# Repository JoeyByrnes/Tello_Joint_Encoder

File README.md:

# Tello_Joint_Encoder
PCB Design Files and Firmware for Tello Joint Encoders

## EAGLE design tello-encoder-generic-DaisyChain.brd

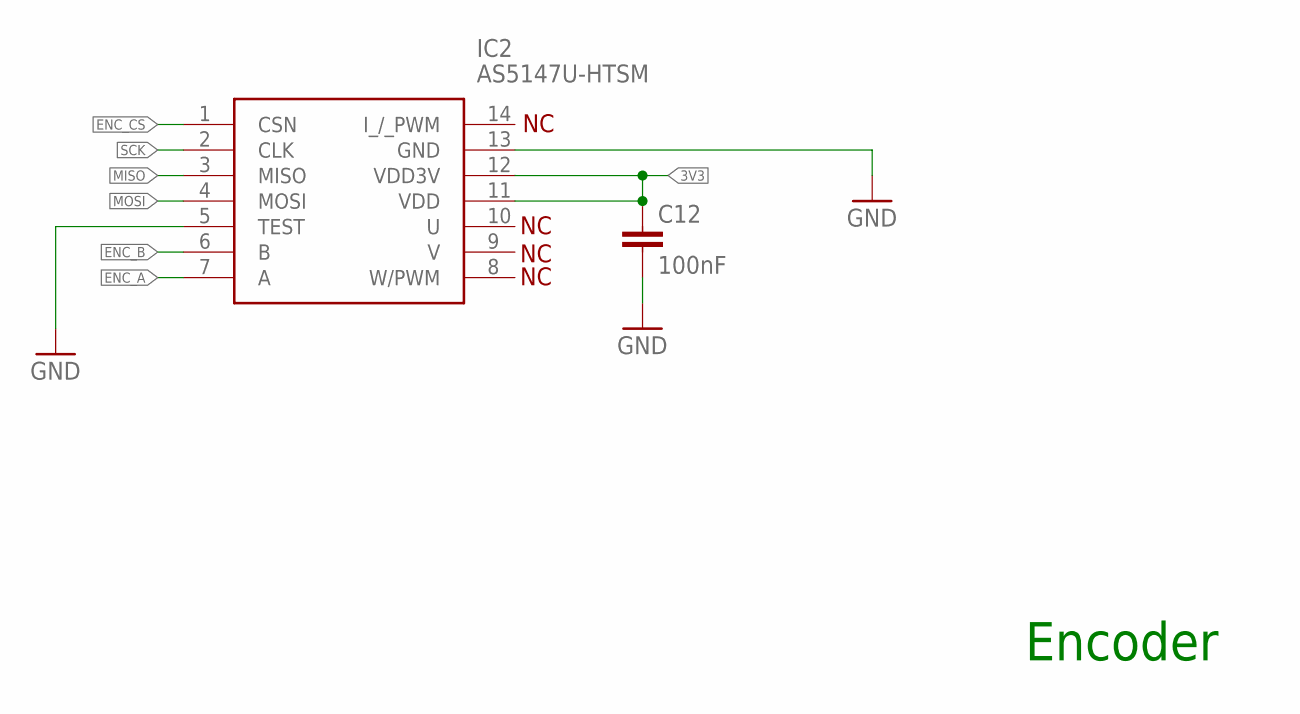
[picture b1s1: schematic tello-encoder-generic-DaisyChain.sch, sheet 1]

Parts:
C12: 100nF; C0402
IC2: AS5147U-HTSM; SOP65P640X120-14N

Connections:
3V3: C12.1, IC2.11 (VDD), IC2.12 (VDD3V); also elsewhere on the board
ENC_A: IC2.7 (A); also elsewhere on the board
ENC_B: IC2.6 (B); also elsewhere on the board
ENC_CS: IC2.1 (CSN); also elsewhere on the board
GND: C12.2, IC2.5 (TEST), IC2.13 (GND); also elsewhere on the board
MISO: IC2.3 (MISO); also elsewhere on the board
MOSI: IC2.4 (MOSI); also elsewhere on the board
SCK: IC2.2 (CLK); also elsewhere on the board

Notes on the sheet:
Encoder

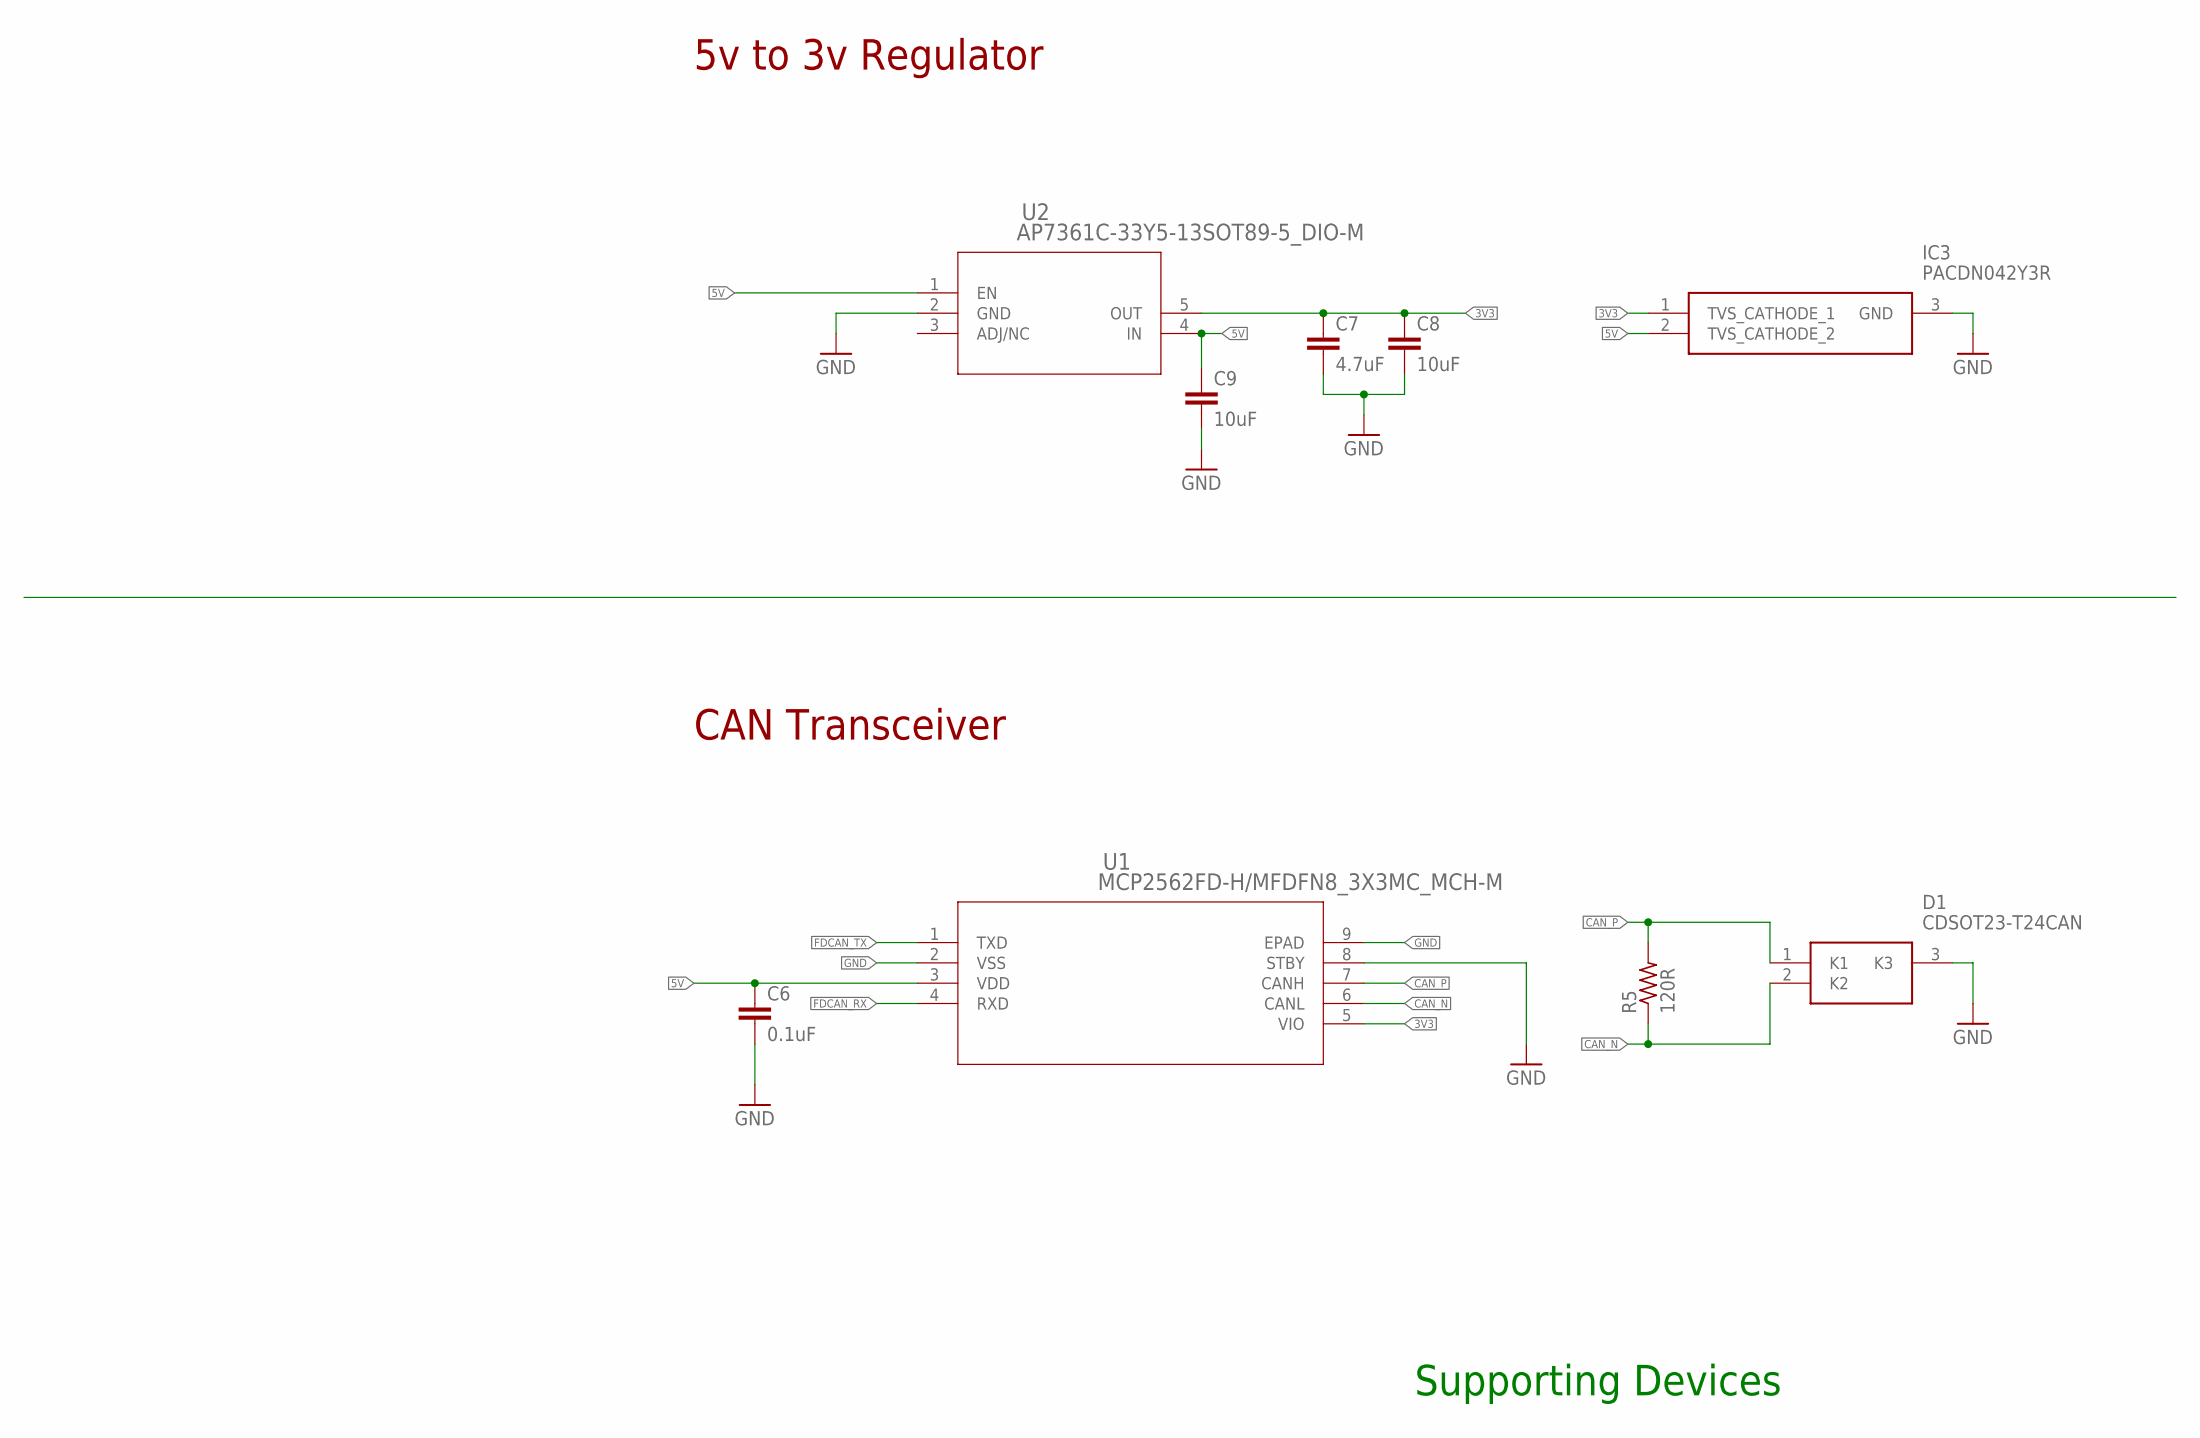
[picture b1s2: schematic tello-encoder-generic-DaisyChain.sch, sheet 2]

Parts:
C6: 0.1uF; C0603
C7: 4.7uF; C0603
C8, C9: 10uF; C0603
D1: CDSOT23-T24CAN; SOT95P230X117-3N
IC3: PACDN042Y3R; SOT96P237X111-3N
R5: 120R; R0402
U1: MCP2562FD-H/MFDFN8_3X3MC_MCH-M; DFN8_3X3MC_MCH-M
U2: AP7361C-33Y5-13SOT89-5_DIO-M; SOT89-5_DIO-M

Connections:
3V3: C7.1, C8.1, IC3.1 (TVS_CATHODE_1), U1.5 (VIO), U2.5 (OUT); also elsewhere on the board
5V: C6.1, C9.1, IC3.2 (TVS_CATHODE_2), U1.3 (VDD), U2.1 (EN), U2.4 (IN); also elsewhere on the board
CAN_N: D1.2 (K2), R5.1, U1.6 (CANL); also elsewhere on the board
CAN_P: D1.1 (K1), R5.2, U1.7 (CANH); also elsewhere on the board
FDCAN_RX: U1.4 (RXD); also elsewhere on the board
FDCAN_TX: U1.1 (TXD); also elsewhere on the board
GND: C6.2, C7.2, C8.2, C9.2, D1.3 (K3), IC3.3 (GND), U1.2 (VSS), U1.8 (STBY), U1.9 (EPAD), U2.2 (GND); also elsewhere on the board

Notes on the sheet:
5v to 3v Regulator
CAN Transceiver
Supporting Devices

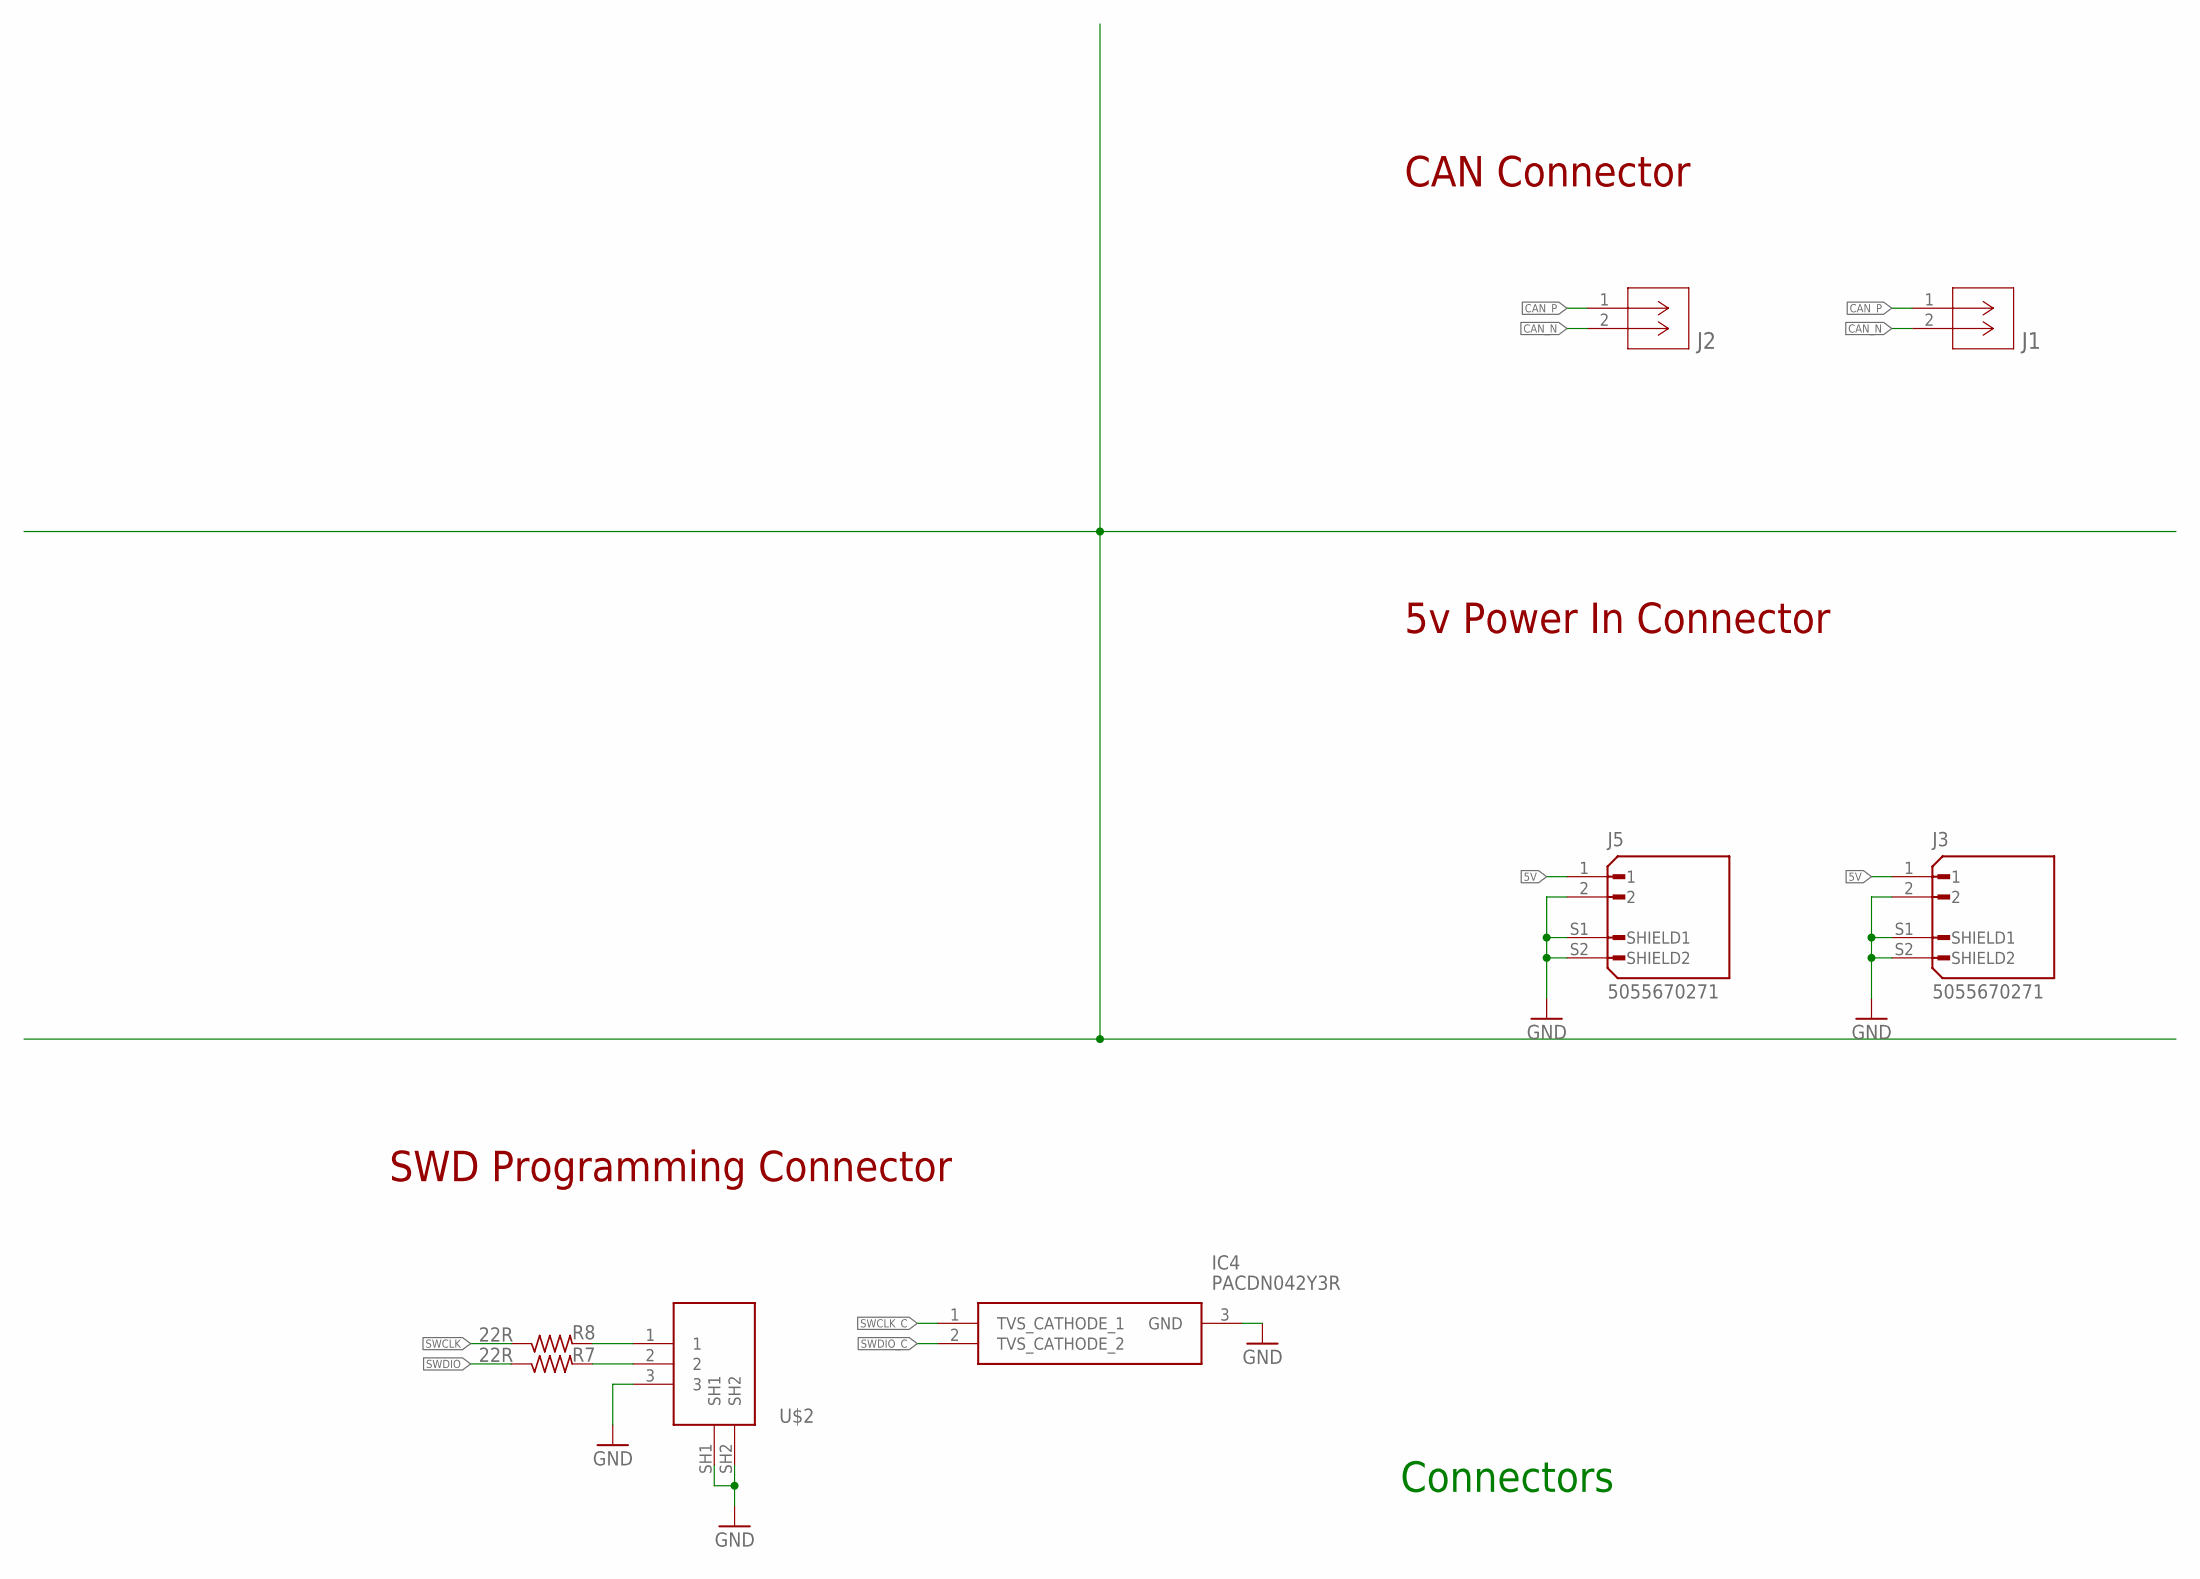
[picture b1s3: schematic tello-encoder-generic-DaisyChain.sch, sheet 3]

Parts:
IC4: PACDN042Y3R; SOT96P237X111-3N
J1, J2: SM02BGHSTBLFSN; CONN_SM02BGHSTB_JST
J3, J5: 5055670271; MOLEX_5055670271
R7, R8: 22R; R0402
U$2: 125SH-G-03-TR-SMT

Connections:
5V: J3.1, J5.1; also elsewhere on the board
CAN_N: J1.2, J2.2; also elsewhere on the board
CAN_P: J1.1, J2.1; also elsewhere on the board
GND: IC4.3 (GND), J3.2, J3.S1 (SHIELD1), J3.S2 (SHIELD2), J5.2, J5.S1 (SHIELD1), J5.S2 (SHIELD2), U$2.3, U$2.SH1, U$2.SH2; also elsewhere on the board
SWCLK: R8.1; also elsewhere on the board
SWCLK_C: IC4.1 (TVS_CATHODE_1), R8.2, U$2.1
SWDIO: R7.1; also elsewhere on the board
SWDIO_C: IC4.2 (TVS_CATHODE_2), R7.2, U$2.2

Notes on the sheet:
U$2
CAN Connector
5v Power In Connector
SWD Programming Connector
Connectors

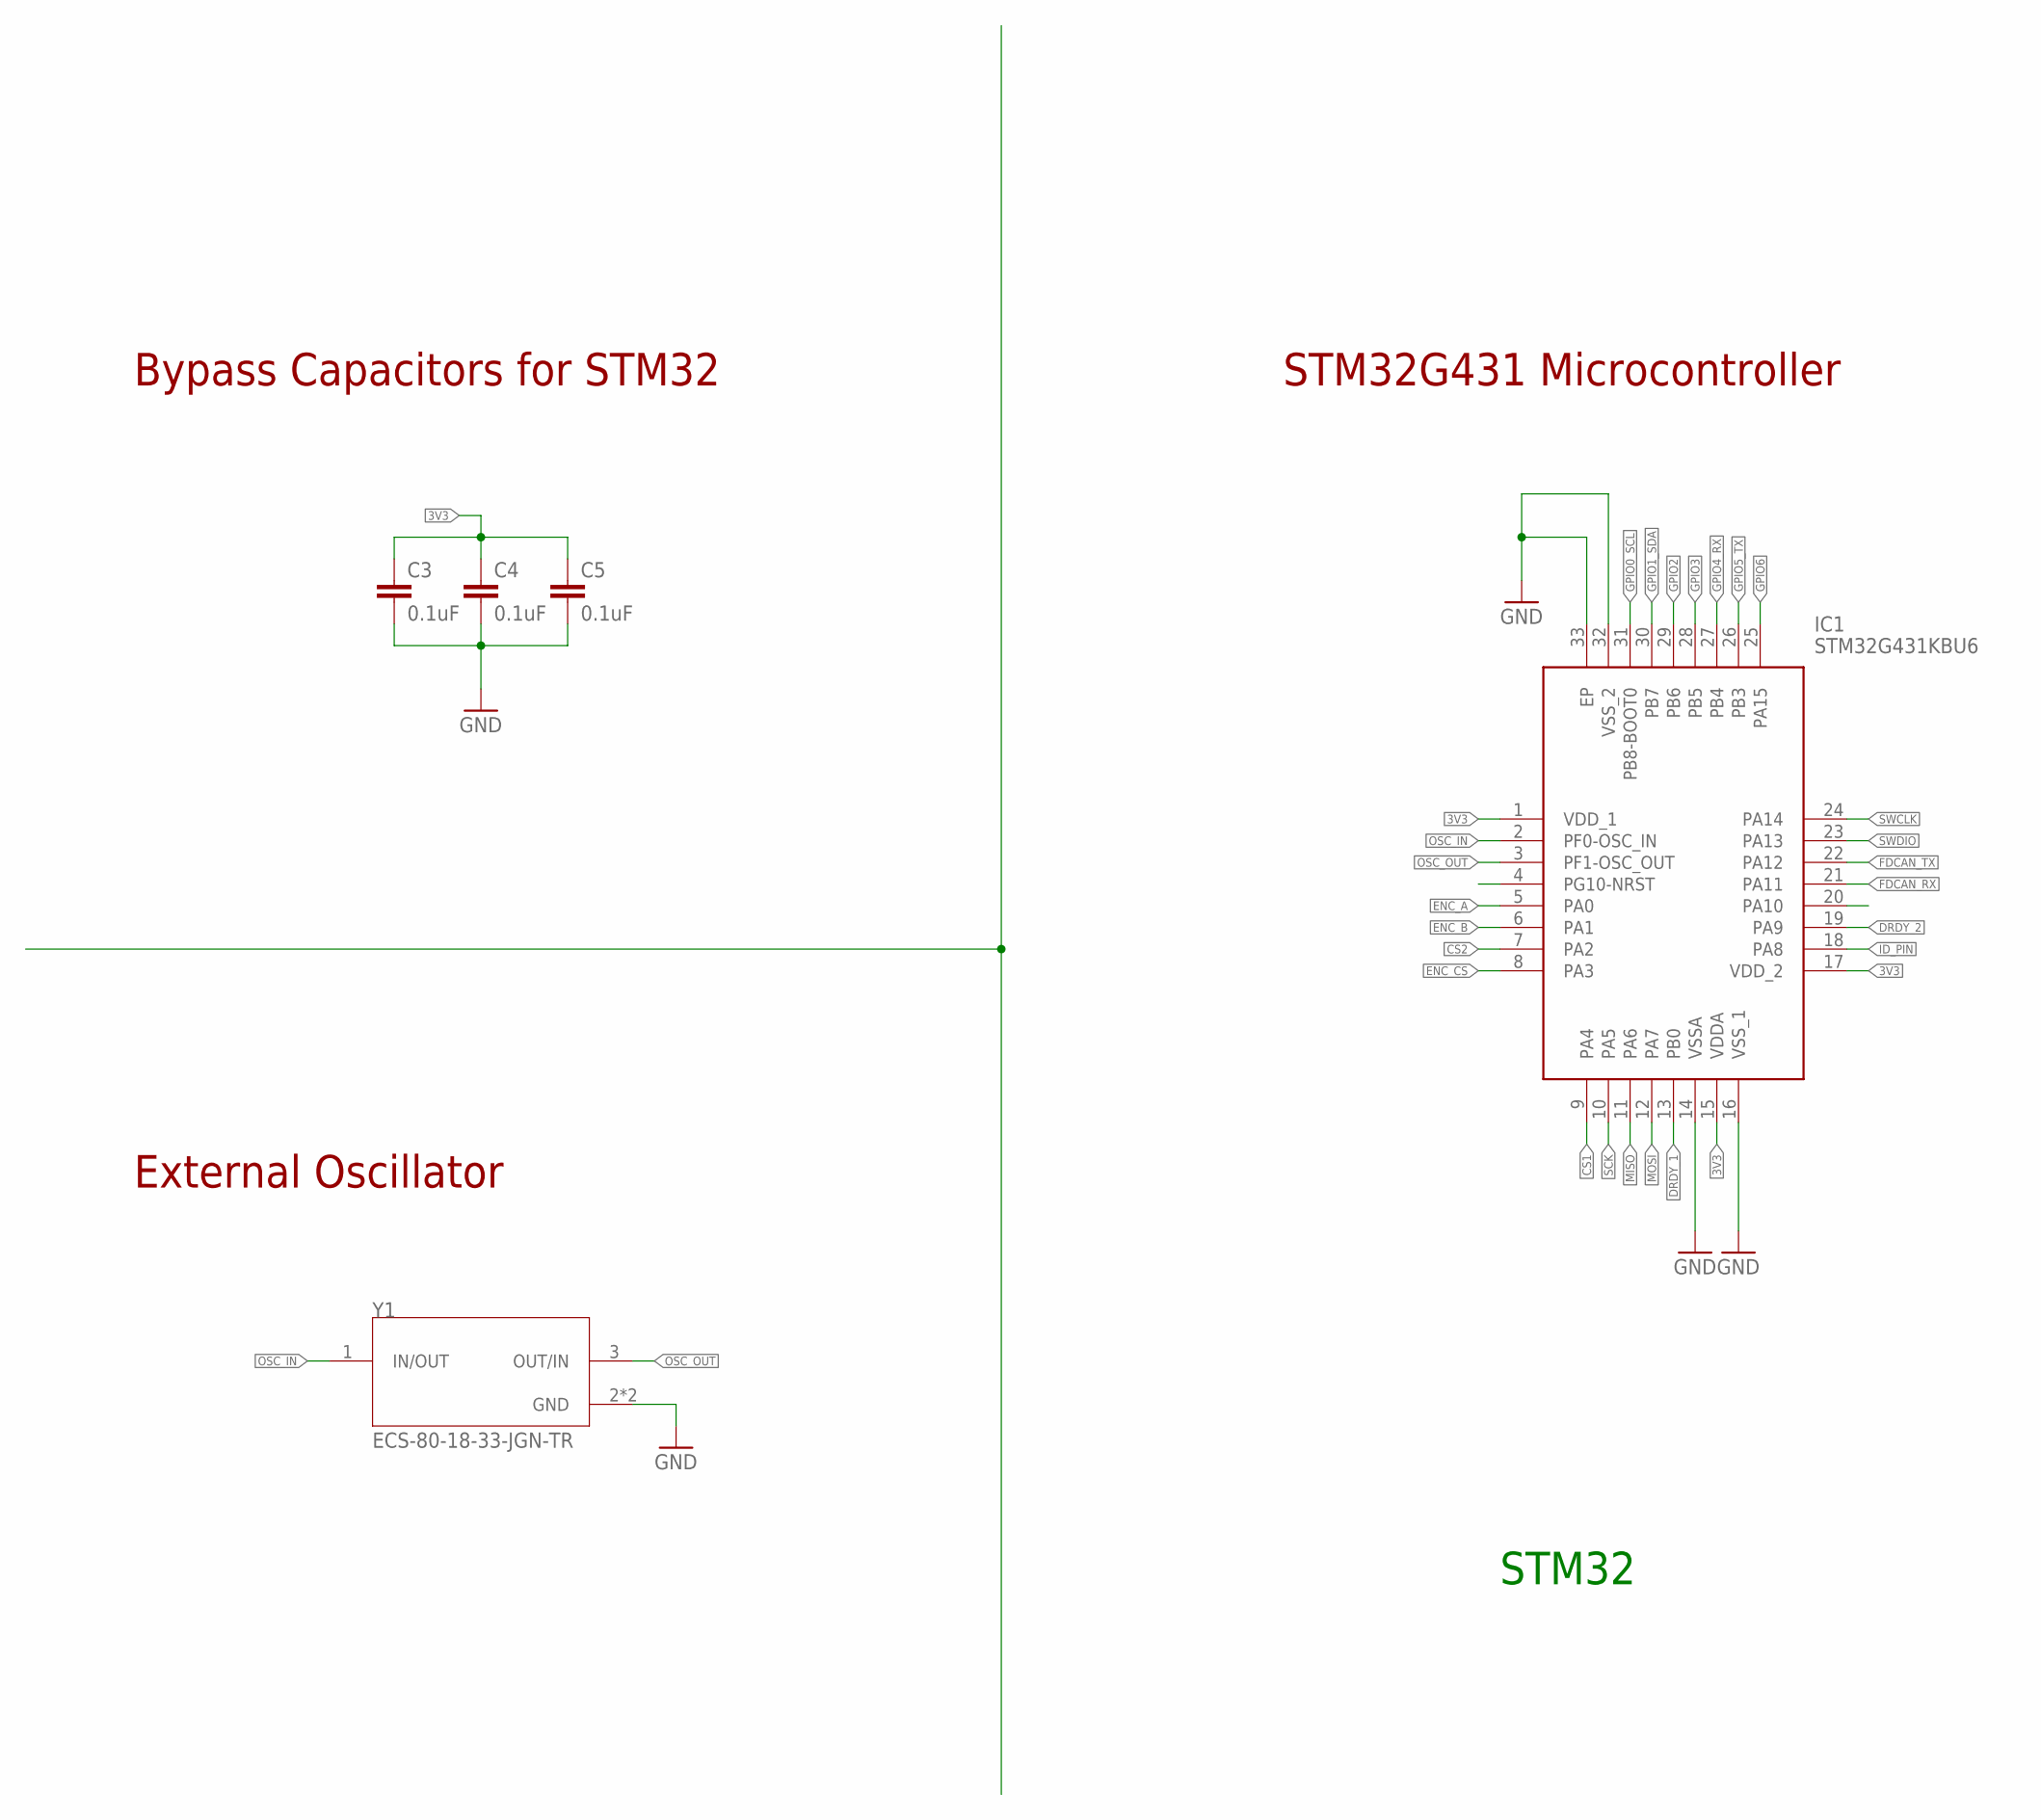
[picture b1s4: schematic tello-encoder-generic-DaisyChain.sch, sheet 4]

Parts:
C3, C4, C5: 0.1uF; C0402
IC1: STM32G431KBU6; QFN50P500X500X60-33N
Y1: ECS-80-18-33-JGN-TR; XTAL_ECS-240-8-33-AGN-TR

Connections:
3V3: C3.1, C4.1, C5.1, IC1.1 (VDD_1), IC1.15 (VDDA), IC1.17 (VDD_2); also elsewhere on the board
CS1: IC1.9 (PA4)
CS2: IC1.7 (PA2)
DRDY_1: IC1.13 (PB0)
DRDY_2: IC1.19 (PA9)
ENC_A: IC1.5 (PA0); also elsewhere on the board
ENC_B: IC1.6 (PA1); also elsewhere on the board
ENC_CS: IC1.8 (PA3); also elsewhere on the board
FDCAN_RX: IC1.21 (PA11); also elsewhere on the board
FDCAN_TX: IC1.22 (PA12); also elsewhere on the board
GND: C3.2, C4.2, C5.2, IC1.14 (VSSA), IC1.16 (VSS_1), IC1.32 (VSS_2), IC1.33 (EP), Y1.2 (GND), Y1.4 (GND); also elsewhere on the board
GPIO0_SCL: IC1.31 (PB8-BOOT0)
GPIO1_SDA: IC1.30 (PB7)
GPIO2: IC1.29 (PB6)
GPIO3: IC1.28 (PB5)
GPIO4_RX: IC1.27 (PB4)
GPIO5_TX: IC1.26 (PB3)
GPIO6: IC1.25 (PA15)
ID_PIN: IC1.18 (PA8)
MISO: IC1.11 (PA6); also elsewhere on the board
MOSI: IC1.12 (PA7); also elsewhere on the board
OSC_IN: IC1.2 (PF0-OSC_IN), Y1.1 (IN/OUT)
OSC_OUT: IC1.3 (PF1-OSC_OUT), Y1.3 (OUT/IN)
SCK: IC1.10 (PA5); also elsewhere on the board
SWCLK: IC1.24 (PA14); also elsewhere on the board
SWDIO: IC1.23 (PA13); also elsewhere on the board

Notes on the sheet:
Bypass Capacitors for STM32
External Oscillator
STM32G431 Microcontroller
STM32

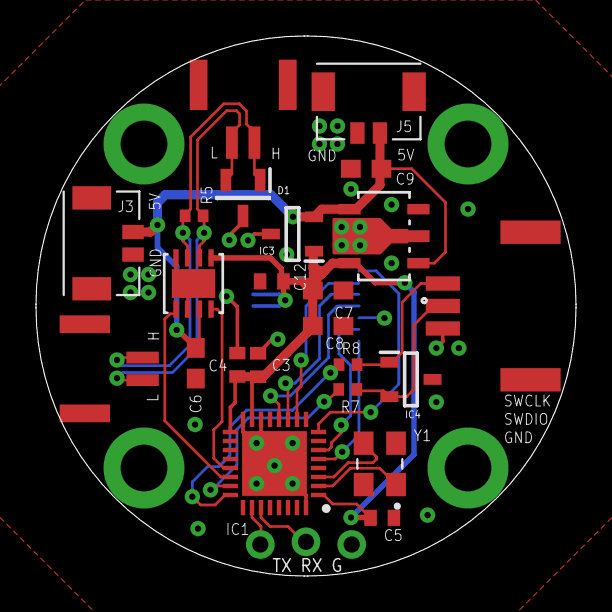
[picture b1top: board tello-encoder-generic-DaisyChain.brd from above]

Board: 4 copper layers, 30.0 x 30.0 mm, 24 parts (1 on the bottom side), 19 nets.

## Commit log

2023-10-04 added design files and frmware
2023-10-04 added design files and firmware

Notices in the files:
parts and their libraries:
COPYRIGHT: Copyright (C) 2023 Ultra Librarian. All rights reserved.
COPYRIGHT: Copyright (C) 2022 Ultra Librarian. All rights reserved.
